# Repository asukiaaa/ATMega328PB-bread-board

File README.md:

# ATmega328PB-bread-board

[schema](/docs/ATmega328PB-bread-board.pdf)

## License

MIT

## References

- [ATmega328PB datasheet (PDF)](http://ww1.microchip.com/downloads/en/DeviceDoc/40001906A.pdf)
- [MiniCore](https://github.com/MCUdude/MiniCore)
- [MiniCore/avr/variants/pb-variant/pins_arduino.h](https://github.com/MCUdude/MiniCore/blob/master/avr/variants/pb-variant/pins_arduino.h)

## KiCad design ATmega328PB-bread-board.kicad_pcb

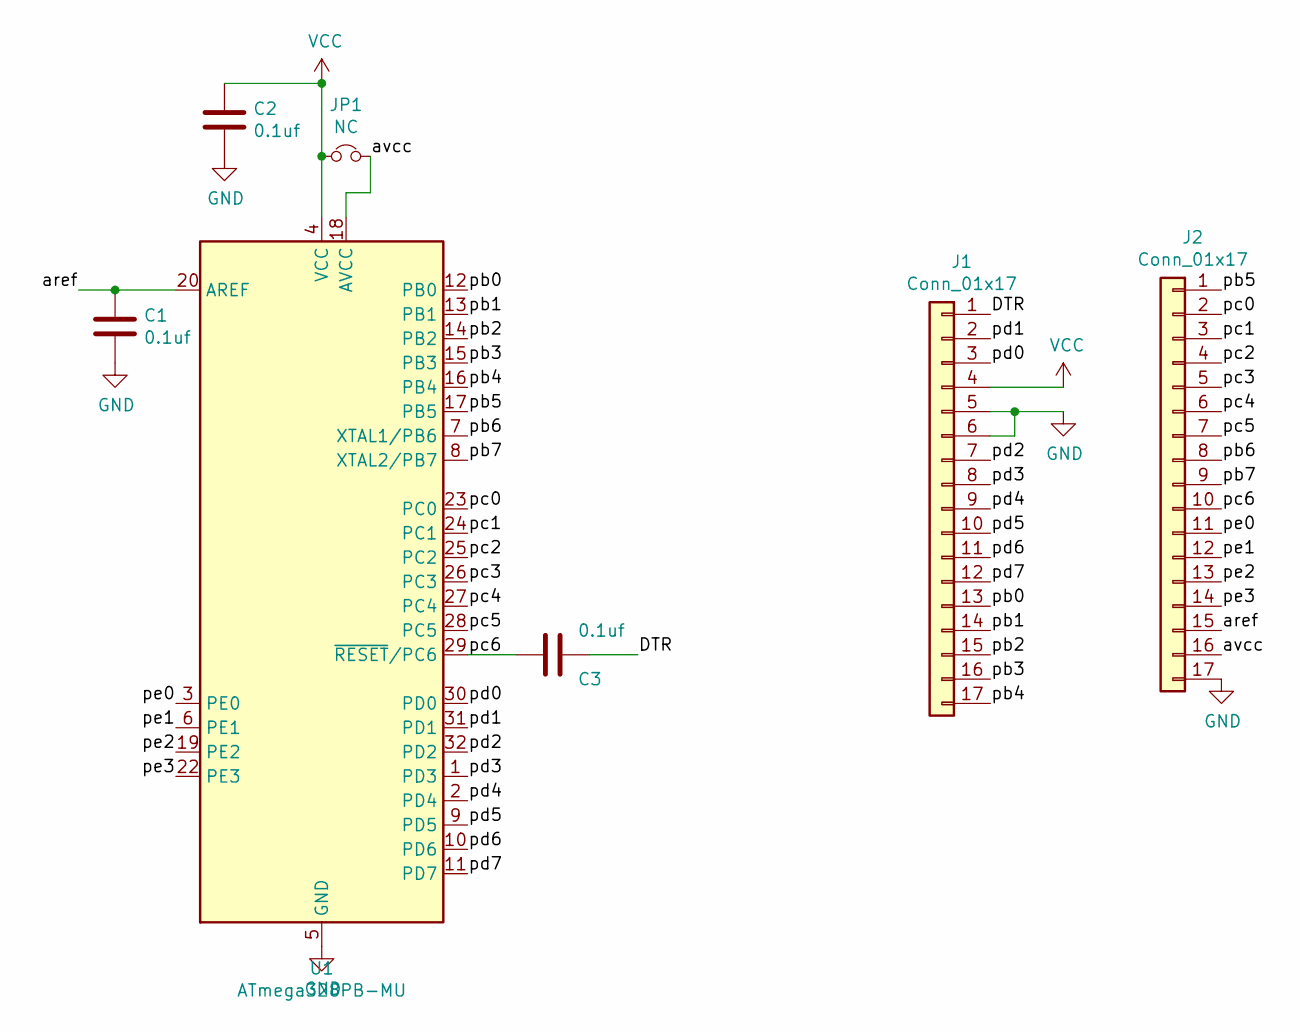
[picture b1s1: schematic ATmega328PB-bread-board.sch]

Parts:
C1, C2, C3: 0.1uf; C_0402_1005Metric
J1, J2: Conn_01x17; PinSocket_1x17_P2.54mm_Vertical
JP1: NC; SolderJumper-2_P1.3mm_Bridged_RoundedPad1.0x1.5mm
U1: ATmega328PB-MU; QFN-32-1EP_5x5mm_P0.5mm_EP3.1x3.1mm

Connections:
/DTR: C3.1, J1.1
/aref: C1.1, J2.15, U1.20 (AREF)
/avcc: J2.16, JP1.2, U1.18 (AVCC)
/pb0: J1.13, U1.12 (PB0)
/pb1: J1.14, U1.13 (PB1)
/pb2: J1.15, U1.14 (PB2)
/pb3: J1.16, U1.15 (PB3)
/pb4: J1.17, U1.16 (PB4)
/pb5: J2.1, U1.17 (PB5)
/pb6: J2.8, U1.7 (XTAL1/PB6)
/pb7: J2.9, U1.8 (XTAL2/PB7)
/pc0: J2.2, U1.23 (PC0)
/pc1: J2.3, U1.24 (PC1)
/pc2: J2.4, U1.25 (PC2)
/pc3: J2.5, U1.26 (PC3)
/pc4: J2.6, U1.27 (PC4)
/pc5: J2.7, U1.28 (PC5)
/pc6: C3.2, J2.10, U1.29 (~RESET~/PC6); also elsewhere on the board
/pd0: J1.3, U1.30 (PD0)
/pd1: J1.2, U1.31 (PD1)
/pd2: J1.7, U1.32 (PD2)
/pd3: J1.8, U1.1 (PD3)
/pd4: J1.9, U1.2 (PD4)
/pd5: J1.10, U1.9 (PD5)
/pd6: J1.11, U1.10 (PD6)
/pd7: J1.12, U1.11 (PD7)
/pe0: J2.11, U1.3 (PE0)
/pe1: J2.12, U1.6 (PE1)
/pe2: J2.13, U1.19 (PE2)
/pe3: J2.14, U1.22 (PE3)
GND: C1.2, C2.2, J1.5, J1.6, J2.17, U1.5 (GND), U1.21 (GND), U1.33 (GND)
VCC: C2.1, J1.4, JP1.1, U1.4 (VCC); also elsewhere on the board

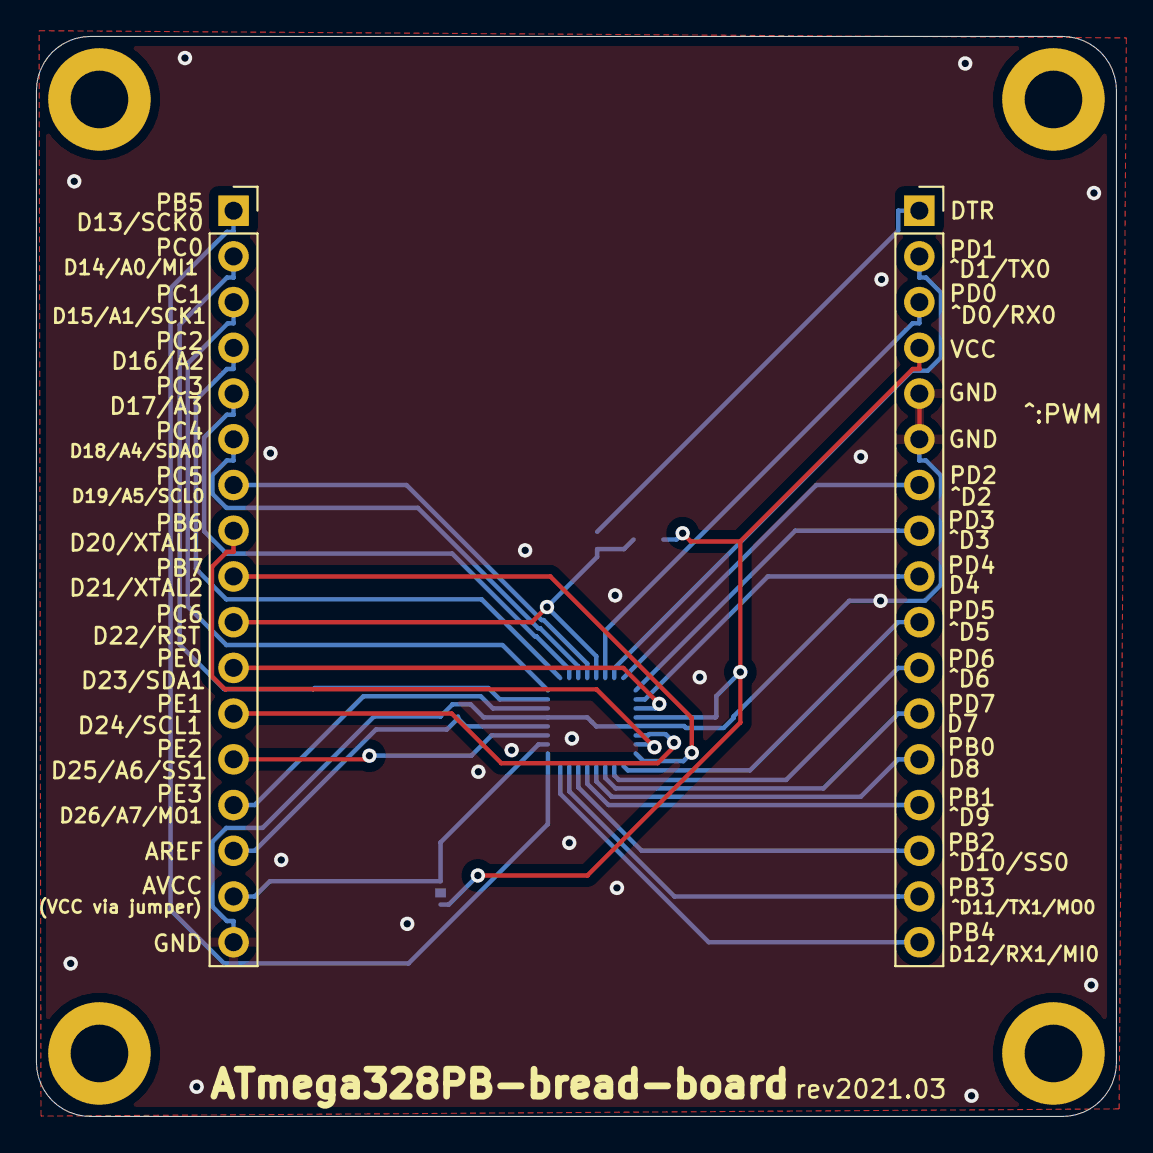
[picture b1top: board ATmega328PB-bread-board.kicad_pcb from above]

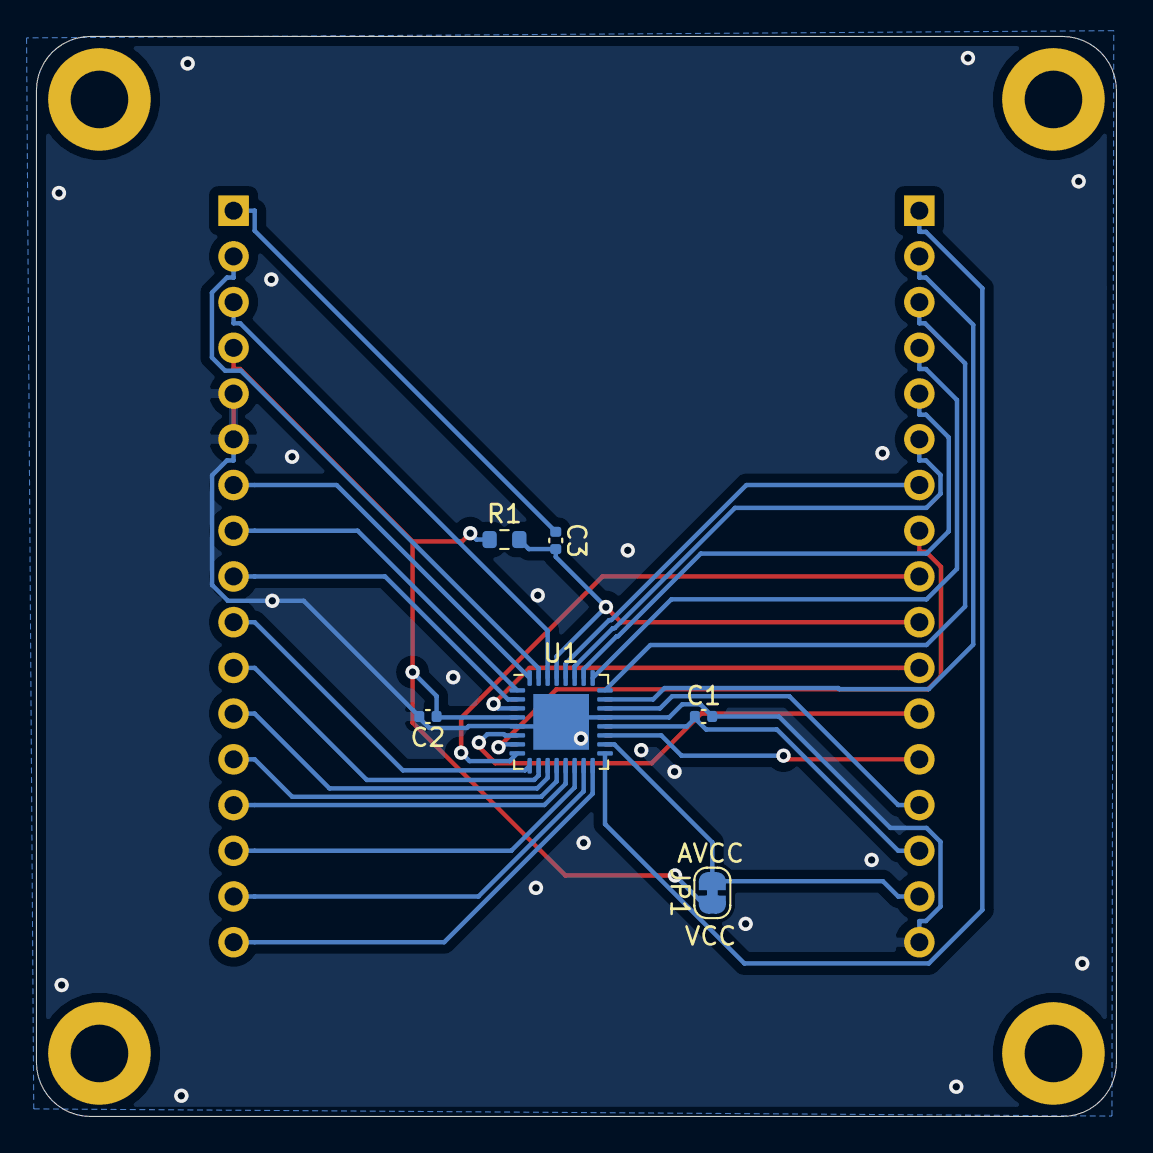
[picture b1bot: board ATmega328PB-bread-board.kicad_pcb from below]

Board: 2 copper layers, 60.0 x 60.0 mm, 12 parts (6 on the bottom side), 32 nets.

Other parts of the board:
R1: 10k; R_0603_1608Metric
REF1, REF2, REF3, REF4: MountingHole_3.2mm_M3_ISO7380_Pad

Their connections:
/pc6: R1.2; also elsewhere on the board
VCC: R1.1; also elsewhere on the board

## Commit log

2020-07-12 Add size info to pcb
2020-07-12 Add schema and size image
2021-03-14 Add a link of my blog on readme
2021-03-14 Add DTR pin and change pin layout
2021-03-14 Move position of mouting holes 0.5mm inside
2021-03-14 Update drawing size for mountig hole position
2021-03-14 Update gnd via position
2021-03-30 Remove mask for jumper
2021-04-12 Add pullup resistor to RST
